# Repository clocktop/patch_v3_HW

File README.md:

# patch_v3_kicad
Kicad Files for V3 of the wireless sensing patch

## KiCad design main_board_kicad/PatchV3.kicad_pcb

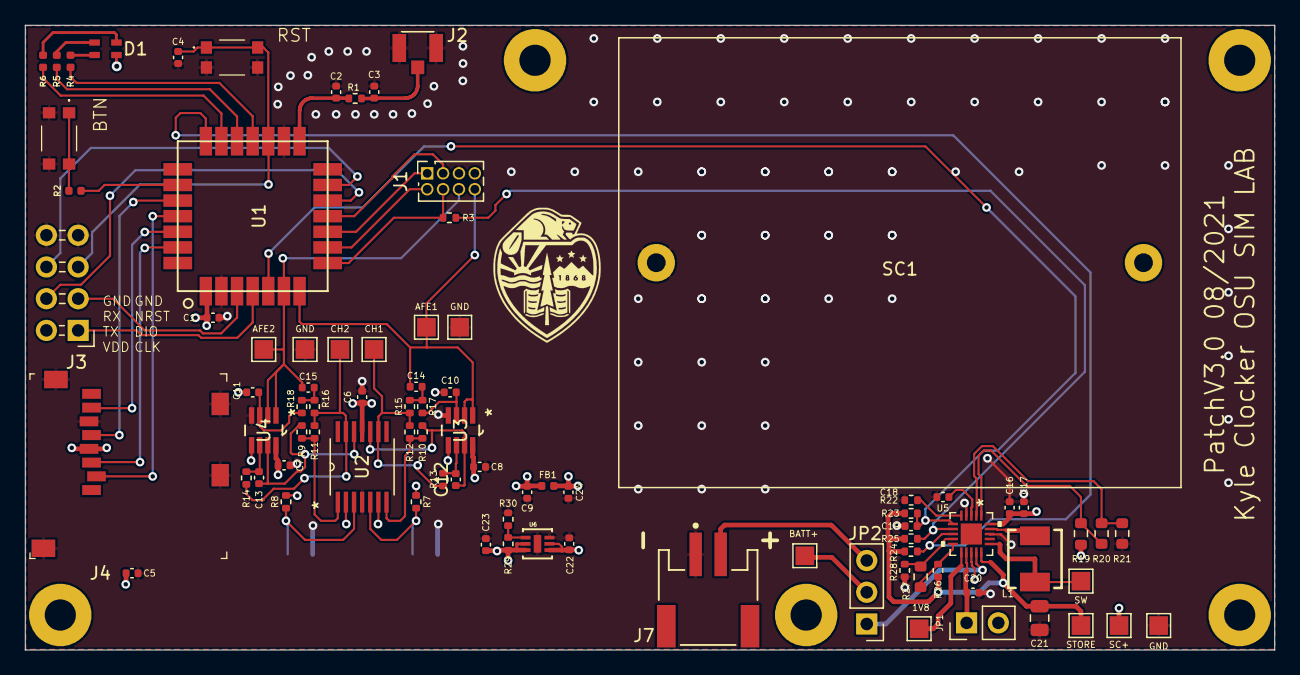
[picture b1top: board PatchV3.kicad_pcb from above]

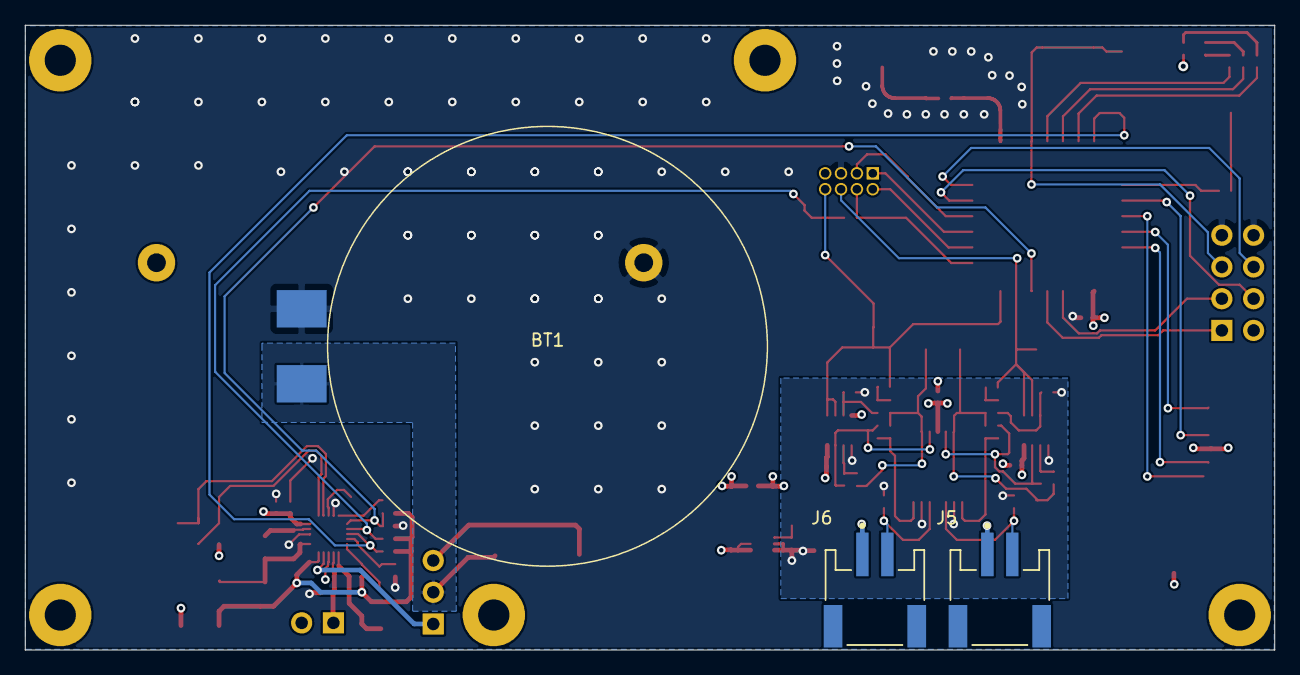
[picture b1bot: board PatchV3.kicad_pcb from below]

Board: 4 copper layers, 100.0 x 50.0 mm, 88 parts (3 on the bottom side), 62 nets.

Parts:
1V8: TestPoint; TestPoint_Pad_1.5x1.5mm
AFE1, AFE2: TestPoint; TestPoint_Pad_1.5x1.5mm
BATT+: TestPoint; TestPoint_Pad_1.5x1.5mm
BT1: 3.7V 500mAh; RJD-ST1
BTN: KMR742NGLFS
C1, C4, C5, C6, C7, C8, C9, C12, C13, C17, C19, C22, C23, C24: 0.1uF; C_0402_1005Metric
C2, C3: DNP; C_0402_1005Metric
C10, C11, C14, C15: 220p; C_0402_1005Metric
C16, C20: 10uF; C_0402_1005Metric
C18: 10nF; C_0402_1005Metric
C21: 47uF; C_0805_2012Metric
CH1, CH2: TestPoint; TestPoint_Pad_1.5x1.5mm
D1: LED_ARGB; LED_1.6x1.6
FB1: 600 Ohm; L_0402_1005Metric
GND: TestPoint; TestPoint_Pad_1.5x1.5mm
GND#2, GND#3: TestPoint; TestPoint_Pad_1.5x1.5mm
J1: Conn_02x04_Counter_Clockwise; PinSocket_2x04_P1.27mm_Vertical
J2: U.FL-R-SMT(01); HRS_U.FL-R-SMT(01)
J3: Conn_02x04_Odd_Even; PinHeader_2x04_P2.54mm_Horizontal
J4: 2908-05WB-MG; MicroSD_2908-05WB-MG
J5, J6, J7: JST PH SM4 S2B; JST-S2B-PH-SM4-TBLFSN-Manufacturer_Recommended
JP1: Jumper; PinHeader_1x02_P2.54mm_Vertical
JP2: Jumper_NC_Dual; PinHeader_1x03_P2.54mm_Vertical
L1: 22uH; WE-LHMI_4020
R1, R3, R22: 0; R_0402_1005Metric
R2, R4, R5, R6: 1.5k; R_0402_1005Metric
R7, R8: 1M 0.1%; R_0402_1005Metric
R9, R10: 10k 0.1%; R_0402_1005Metric
R11, R12, R15, R16, R17, R18: 90.9k 0.1%; R_0402_1005Metric
R13, R14: 632k 0.1%; R_0402_1005Metric
R19: 10M; R_0603_1608Metric
R20: 909k; R_0603_1608Metric
R21: 3.83M; R_0603_1608Metric
R23, R29: 1M 1%; R_0402_1005Metric
R24, R25: 10M; R_0402_1005Metric
R26: 6.04M; R_0402_1005Metric
R27: 1.05M; R_0603_1608Metric
R28: 2.94M; R_0402_1005Metric
R30: 590k 1%; R_0402_1005Metric
RST: KMR742NGLFS
SC1: Solar_Cell; SM141K10LV
SC+: TestPoint; TestPoint_Pad_1.5x1.5mm
STORE: TestPoint; TestPoint_Pad_1.5x1.5mm
SW: TestPoint; TestPoint_Pad_1.5x1.5mm
U1: LoRa-E5
U2: INA2321EA_250; INA2321EA&slash_250
U3, U4: OPA2349EA_250; OPA2349EA
U5: SPV1050TTR
U6: LT3009IDCTRMPBF; DFN-6_DC

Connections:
/AFE_CH1: AFE1.1, C14.1, J1.8, U1.7, U3.1, U3.2
/AFE_CH2: AFE2.1, C15.1, J1.6, U1.6, U4.1, U4.2
/BTN: R2.1, U1.23
/Contact Mic AFE/REFA: C13.1, R9.2, U2.12, U4.7
/Contact Mic AFE/REFB: C12.1, R10.2, U2.10, U3.7
/GPIO0: J1.4, R3.1, U1.8
/GPIO1: J1.2, U1.9
/GPIO2: J1.1, U1.10
/GPIO3: J1.3, U1.11
/Havester and Power/BATT: JP2.1, U5.14
/Havester and Power/BATT_CHG: J7.2, JP2.3
/Havester and Power/SC+: C16.1, C17.1, R19.1, SC1.1, SC+.1, U5.13, U5.20
/Havester and Power/STORE: C21.1, R23.2, R24.1, R25.1, R26.1, STORE.1, U5.15
/Havester and Power/SW: L1.2, SW.1, U5.16
/LDO_3V3_EN: C19.1, R23.1, U1.5, U5.6
/LED_B: R6.1, U1.20
/LED_G: R5.1, U1.19
/LED_R: R4.1, U1.18
/LPUART_RX: J3.6, U1.13
/LPUART_TX: J3.4, U1.12
/NRST: C4.1, J3.5, RST.1, RST.4, U1.17
/RFIO: C2.1, R1.1, U1.15
/RFIO_ANT: C3.1, J2.3, R1.2
/SD_CLK: J4.5, U1.24
/SD_CS: J4.2, U1.25
/SD_MISO: J4.7, U1.26
/SD_MOSI: J4.3, U1.27
/SW_CLK: J3.1, U1.4
/SW_DIO: J3.3, U1.3
/~BATT_CHG: R3.2, R25.2, U5.7
/~BATT_CONN: R24.2, U1.21, U5.8
GND: BT1.2, BTN.2, BTN.3, C1.2, C2.2, C3.2, C4.2, C5.2, C6.2, C7.2, C8.2, C9.2, C16.2, C17.2, C18.2, C19.2, C20.2, C21.2, C22.2, C23.2, C24.2, GND.1, GND#2.1, GND#3.1, J1.5, J2.1, J2.2, J3.7, J3.8, J4.6, J4.9, J5.1, J6.1, J7.1, R21.2, R22.2, R28.2, R30.2, RST.2, RST.3, SC1.2, U1.2, U1.14, U1.16, U1.22, U2.4, U3.4, U4.4, U5.4, U5.18, U6.6, U6.7
unnamed: BATT+.1, BT1.1, JP2.2
unnamed: C10.1, R17.1, U3.3
unnamed: C11.1, R18.1, U4.3
unnamed: C12.2, R13.1, U3.6
unnamed: C13.2, R14.1, U4.6
unnamed: C14.2, R15.1, R17.2
unnamed: C15.2, R16.1, R18.2
unnamed: C18.1, U5.3
unnamed: C20.1, JP1.1, U5.12
unnamed: D1.2, R4.2
unnamed: D1.3, R5.2
unnamed: D1.4, R6.2
unnamed: J5.2, R8.2, U2.3
unnamed: J6.2, R7.2, U2.5
unnamed: L1.1, U5.19
unnamed: BTN.1, BTN.4, R2.2
unnamed: R10.1, R12.2, U2.7
unnamed: CH2.1, R11.1, R14.2, R16.2, U2.13
unnamed: R9.1, R11.2, U2.1
unnamed: CH1.1, R12.1, R13.2, R15.2, U2.9
unnamed: R19.2, R20.1, U5.1
unnamed: R20.2, R21.1, U5.2
unnamed: R22.1, U5.5
unnamed: R26.2, R27.1, U5.10
unnamed: R27.2, R28.1, U5.9
unnamed: R29.2, R30.1, U6.1
unnamed: 1V8.1, U5.11
VCOM: C10.2, C11.2, C23.1, R7.1, R8.1, R29.1, U2.2, U2.6, U3.5, U4.5, U6.2, U6.3
VDD: C1.1, C5.1, C22.1, C24.1, D1.1, FB1.2, J1.7, J3.2, J4.4, JP1.2, U1.1, U6.4, U6.5
VDDA: C6.1, C7.1, C8.1, C9.1, FB1.1, U2.11, U3.8, U4.8

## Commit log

2021-07-29 first commit started making a few changes
2021-07-30 redid power section with new energy harverster ic
2021-08-05 catch up
2021-08-07 schematic functionally finished working on layout
2021-08-09 Finished pre-review layout
2021-08-09 fixed a position of a pin header
2021-08-09 reorganized the folder structure
2021-08-12 catchup

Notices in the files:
parts and their libraries:
Copyright 2021 Accelerated Designs. All rights reserved.
Copyright 2016 Accelerated Designs. All rights reserved.
